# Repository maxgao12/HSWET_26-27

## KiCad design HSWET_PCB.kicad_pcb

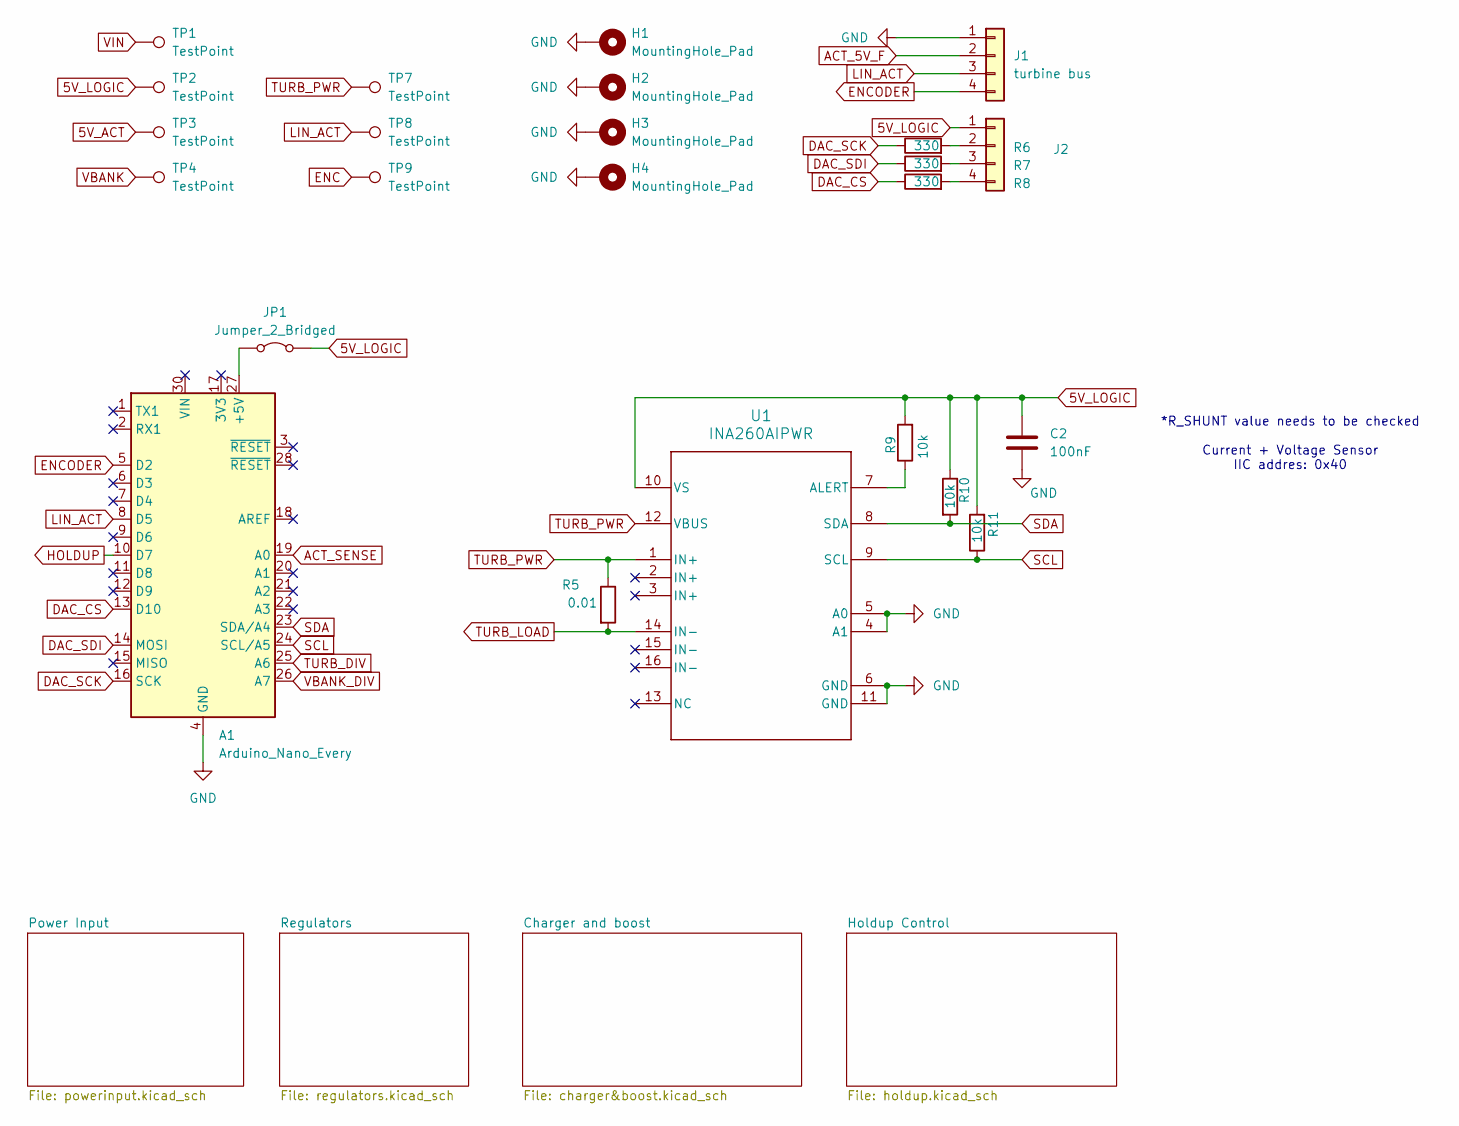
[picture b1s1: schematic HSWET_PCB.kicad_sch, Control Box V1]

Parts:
A1: Arduino_Nano_Every; Arduino_Nano
C2: 100nF; C_0603_1608Metric
H1, H2, H3, H4: MountingHole_Pad; MountingHole_2.5mm_Pad
J1: turbine bus; PinHeader_1x04_P2.54mm_Vertical
J2: turbine bus; PinSocket_1x04_P2.54mm_Vertical
JP1: Jumper_2_Bridged; PinHeader_1x02_P2.54mm_Vertical
R5: 0.01; R_0603_1608Metric
R6, R7, R8: 330; R_0603_1608Metric
R9, R10, R11: 10k; R_0603_1608Metric
TP1, TP2, TP3, TP4, TP7, TP8, TP9: TestPoint; TestPoint_Pad_1.0x1.0mm
U1: INA260AIPWR; ina260

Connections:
5V_ACT: TP3.1 (1_1); also elsewhere on the board
5V_LOGIC: C2.2, J2.1, JP1.2 (B), R9.2, R10.1, R11.2, TP2.1 (1_1), U1.10 (VS); also elsewhere on the board
ACT_5V_F: J1.2; also elsewhere on the board
ACT_SENSE: A1.19 (A0); also elsewhere on the board
DAC_CS: A1.13 (D10), R8.1
DAC_SCK: A1.16 (SCK), R6.1
DAC_SDI: A1.14 (MOSI), R7.1
ENC: TP9.1 (1_1)
ENCODER: A1.5 (D2), J1.4
GND: A1.4 (GND), A1.29 (GND), C2.1, H1.1 (1_1), H2.1 (1_1), H3.1 (1_1), H4.1 (1_1), J1.1, U1.4 (A1), U1.5 (A0), U1.6 (GND), U1.11 (GND); also elsewhere on the board
HOLDUP: A1.10 (D7); also elsewhere on the board
LIN_ACT: A1.8 (D5), J1.3, TP8.1 (1_1)
unnamed: A1.27 (+5V), JP1.1 (A)
unnamed: J2.2, R6.2
unnamed: J2.3, R7.2
unnamed: J2.4, R8.2
unnamed: R9.1, U1.7 (ALERT)
SCL: A1.24 (SCL/A5), R11.1, U1.9 (SCL)
SDA: A1.23 (SDA/A4), R10.2, U1.8 (SDA)
TURB_DIV: A1.25 (A6); also elsewhere on the board
TURB_LOAD: R5.2, U1.14 (IN-); also elsewhere on the board
TURB_PWR: R5.1, TP7.1 (1_1), U1.1 (IN+), U1.12 (VBUS); also elsewhere on the board
VBANK: TP4.1 (1_1); also elsewhere on the board
VBANK_DIV: A1.26 (A7); also elsewhere on the board
VIN: TP1.1 (1_1); also elsewhere on the board

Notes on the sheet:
*R_SHUNT value needs to be checked Current + Voltage Sensor IIC addres: 0x40

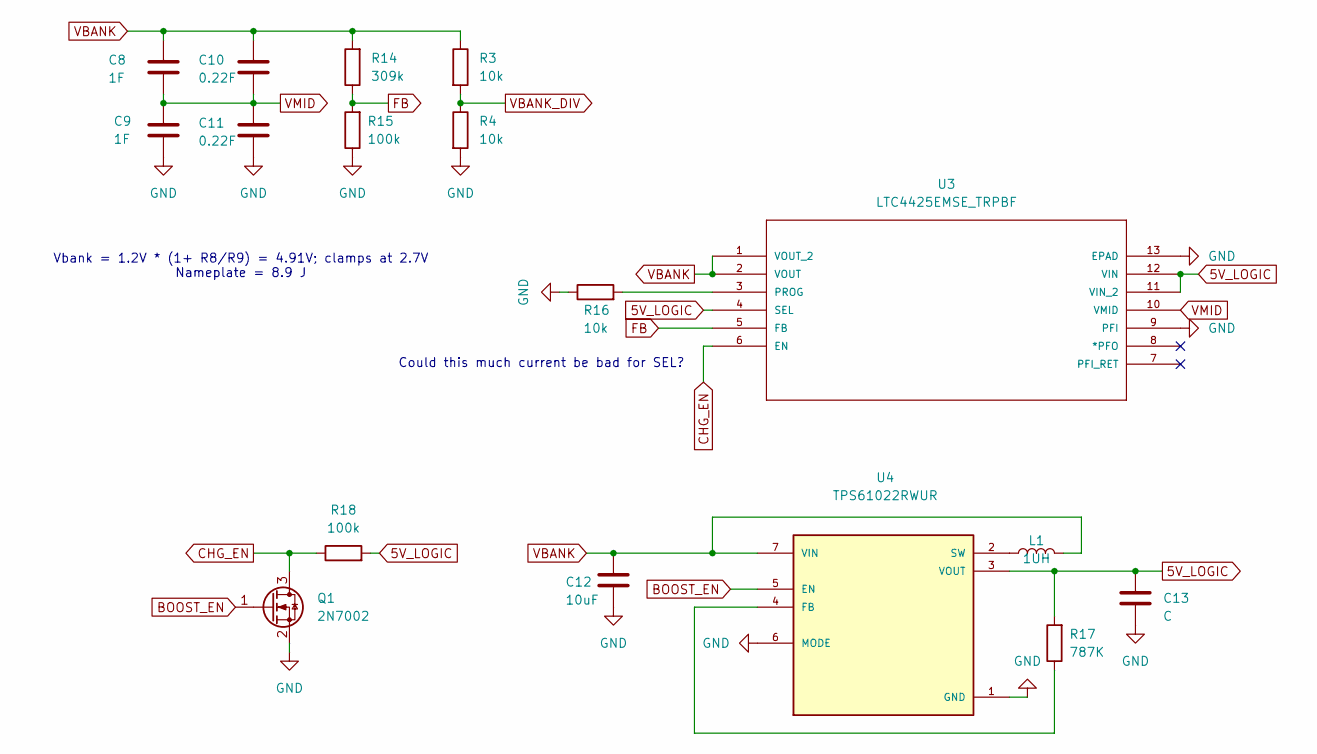
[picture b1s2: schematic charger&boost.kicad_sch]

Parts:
C8, C9: 1F; CAP_DGH-17X17X8.5_ILC
C10, C11: 0.22F; C_0603_1608Metric
C12: 10uF; C_0603_1608Metric
C13: C; C_0603_1608Metric
L1: 1UH; L_Changjiang_FTC201610D
Q1: 2N7002; SOT-23
R3, R4, R16: 10k; R_0603_1608Metric
R14: 309k; R_0603_1608Metric
R15, R18: 100k; R_0603_1608Metric
R17: 787K; R_0603_1608Metric
U3: LTC4425EMSE_TRPBF; MSOP-12_MSE; MANUFACTURER_PART_NUMBER ltc4425emse#pbf
U4: TPS61022RWUR; CONV_TPS61022RWUR; PARTREV 4223724/C 02/2018

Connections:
5V_LOGIC: C13.1, R17.2, R18.2, U3.4 (SEL), U3.11 (VIN_2), U3.12 (VIN), U4.3 (VOUT); also elsewhere on the board
BOOST_EN: Q1.1 (G), U4.5 (EN); also elsewhere on the board
CHG_EN: Q1.3 (D), R18.1, U3.6 (EN)
FB: R14.1, R15.2, U3.5 (FB)
GND: C9.2, C11.2, C12.2, C13.2, Q1.2 (S), R4.2, R15.1, R16.1, U3.9 (PFI), U3.13 (EPAD), U4.1 (GND), U4.6 (MODE); also elsewhere on the board
unnamed: R16.2, U3.3 (PROG)
unnamed: R17.1, U4.4 (FB)
unnamed: L1.2, U4.2 (SW)
VBANK: C8.1, C10.1, C12.1, L1.1, R3.1, R14.2, U3.1 (VOUT_2), U3.2 (VOUT), U4.7 (VIN); also elsewhere on the board
VBANK_DIV: R3.2, R4.1; also elsewhere on the board
VMID: C8.2, C9.1, C10.2, C11.1, U3.10 (VMID)

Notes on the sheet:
Vbank = 1.2V * (1+ R8/R9) = 4.91V; clamps at 2.7V Nameplate = 8.9 J
Could this much current be bad for SEL?

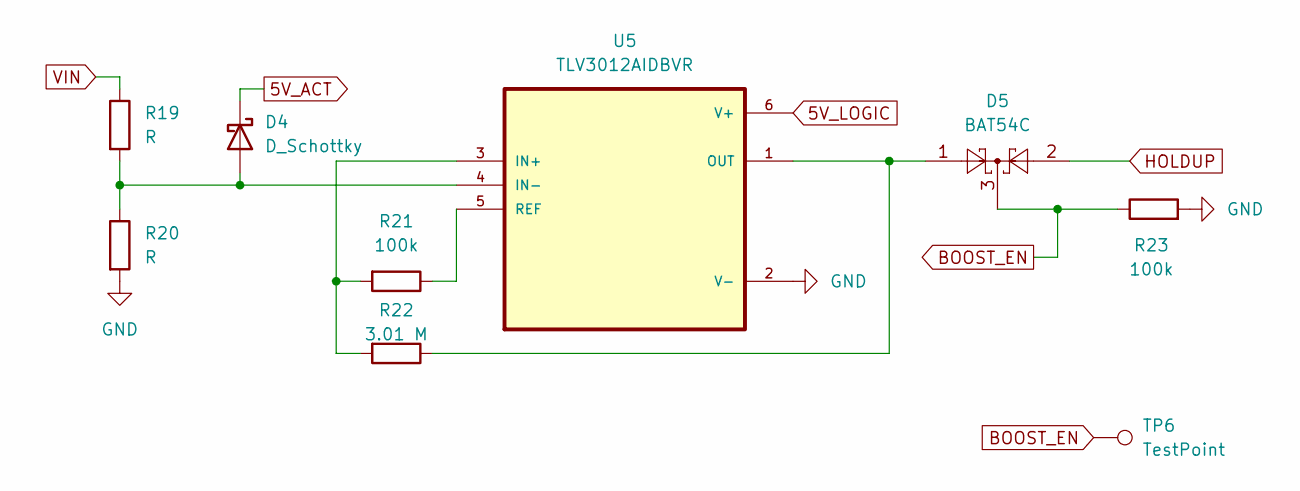
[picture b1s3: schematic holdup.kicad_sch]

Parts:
D4: D_Schottky; DIOM5436X330N
D5: BAT54C; SOT-23
R19, R20: R; R_0603_1608Metric
R21, R23: 100k; R_0603_1608Metric
R22: 3.01 M; R_0603_1608Metric
TP6: TestPoint; TestPoint_Pad_1.0x1.0mm
U5: TLV3012AIDBVR; SOT95P280X145-6N

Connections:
5V_ACT: D4.1 (K); also elsewhere on the board
5V_LOGIC: U5.6 (V+); also elsewhere on the board
BOOST_EN: D5.3, R23.1, TP6.1 (1_1); also elsewhere on the board
GND: R20.2, R23.2, U5.2 (V-); also elsewhere on the board
HOLDUP: D5.2; also elsewhere on the board
unnamed: D4.2 (A), R19.2, R20.1, U5.4 (IN-)
unnamed: R21.2, R22.2, U5.3 (IN+)
unnamed: D5.1, R22.1, U5.1 (OUT)
unnamed: R21.1, U5.5 (REF)
VIN: R19.1; also elsewhere on the board

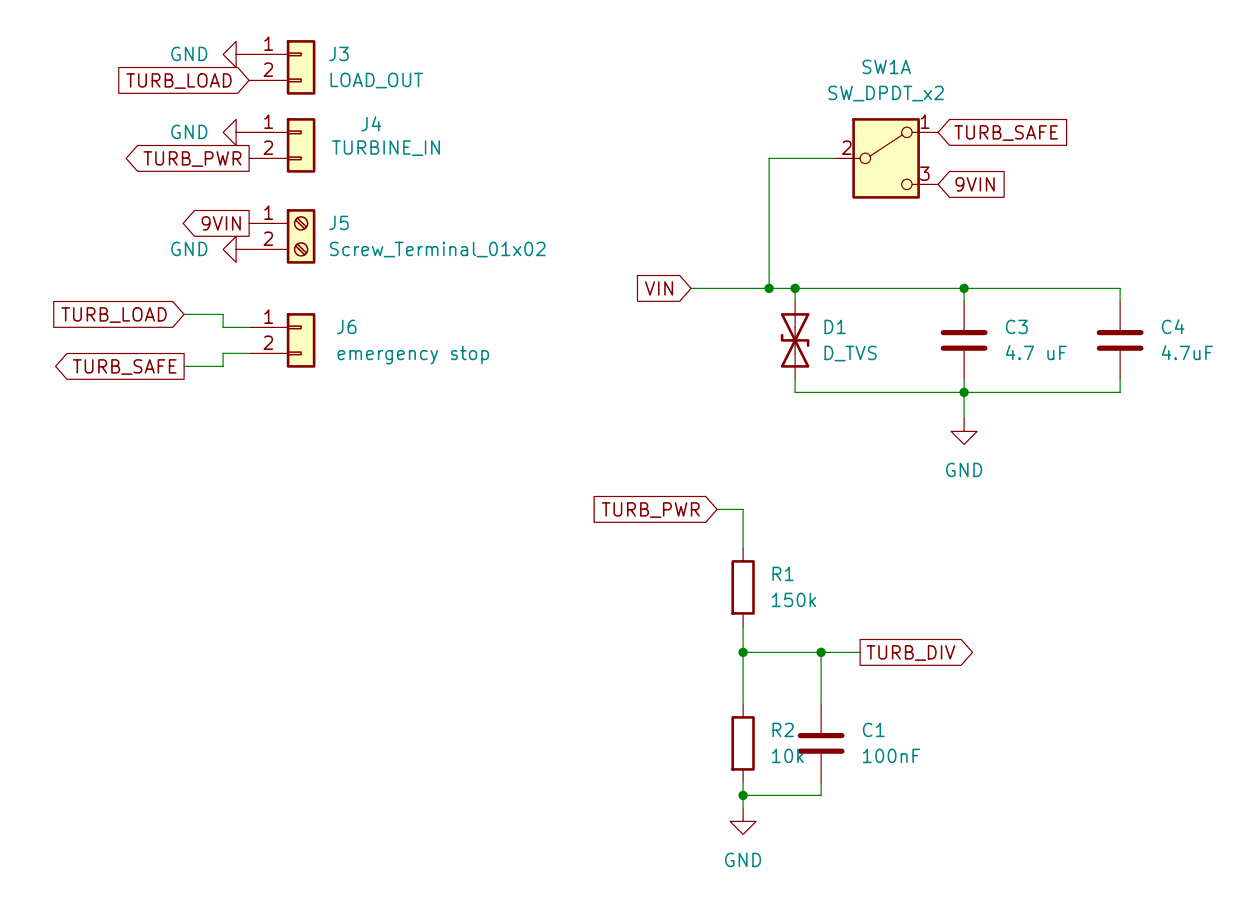
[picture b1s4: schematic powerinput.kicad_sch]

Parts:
C1: 100nF; C_0603_1608Metric
C3: 4.7 uF; C_0603_1608Metric
C4: 4.7uF; C_0603_1608Metric
D1: D_TVS; D_SMB_Handsoldering
J3: LOAD_OUT; AMASS_XT30PW-M_1x02_P2.50mm_Horizontal
J4: TURBINE_IN; AMASS_XT30PW-F_1x02_P2.50mm_Horizontal
J5: Screw_Terminal_01x02; 1760510000
J6: emergency stop; JST_EH_B2B-EH-A_1x02_P2.50mm_Vertical
R1: 150k; R_0603_1608Metric
R2: 10k; R_0603_1608Metric
SW1: SW_DPDT_x2; 1101A2CQEA

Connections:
9VIN: J5.1, SW1.3 (C)
GND: C1.2, C3.2, C4.2, D1.2 (A2), J3.1, J4.1, J5.2, R2.2; also elsewhere on the board
TURB_DIV: C1.1, R1.2, R2.1; also elsewhere on the board
TURB_LOAD: J3.2, J6.1; also elsewhere on the board
TURB_PWR: J4.2, R1.1; also elsewhere on the board
TURB_SAFE: J6.2, SW1.1 (A)
VIN: C3.1, C4.1, D1.1 (A1), SW1.2 (B); also elsewhere on the board

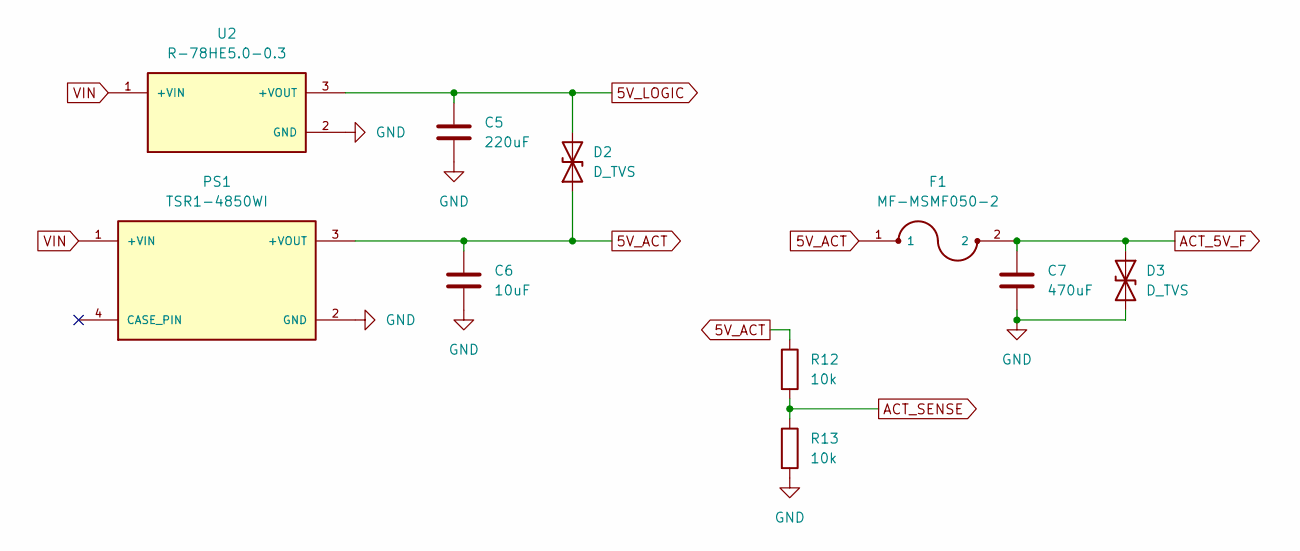
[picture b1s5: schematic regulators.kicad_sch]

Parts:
C5: 220uF; C_0603_1608Metric
C6: 10uF; C_0603_1608Metric
C7: 470uF; C_0603_1608Metric
D2, D3: D_TVS; D_0201_0603Metric_Pad0.64x0.40mm_HandSolder
F1: MF-MSMF050-2; FUSM4632X85
PS1: TSR1-4850WI; CONV_TSR1-4850WI; PARTREV April 7, 2021
R12, R13: 10k; R_0603_1608Metric
U2: R-78HE5.0-0.3; SIP900W75P254L1200H1300Q3; PARTREV 0/2019

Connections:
5V_ACT: C6.1, D2.1 (A1), F1.1, PS1.3 (+VOUT), R12.1; also elsewhere on the board
5V_LOGIC: C5.1, D2.2 (A2), U2.3 (+VOUT); also elsewhere on the board
ACT_5V_F: C7.1, D3.1 (A1), F1.2; also elsewhere on the board
ACT_SENSE: R12.2, R13.1; also elsewhere on the board
GND: C5.2, C6.2, C7.2, D3.2 (A2), PS1.2 (GND), R13.2, U2.2 (GND); also elsewhere on the board
VIN: PS1.1 (+VIN), U2.1 (+VIN); also elsewhere on the board

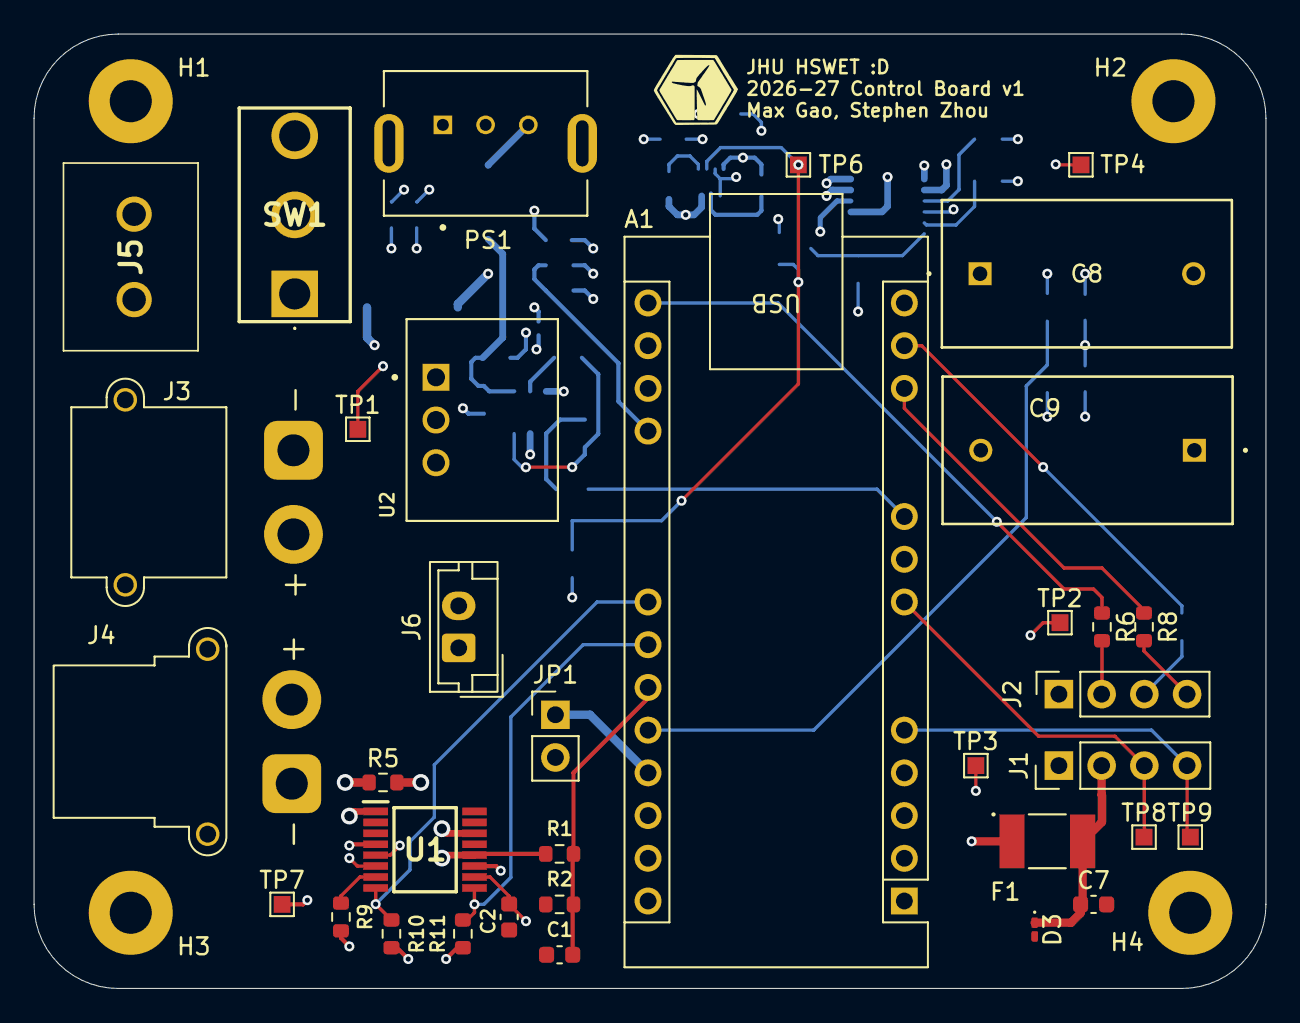
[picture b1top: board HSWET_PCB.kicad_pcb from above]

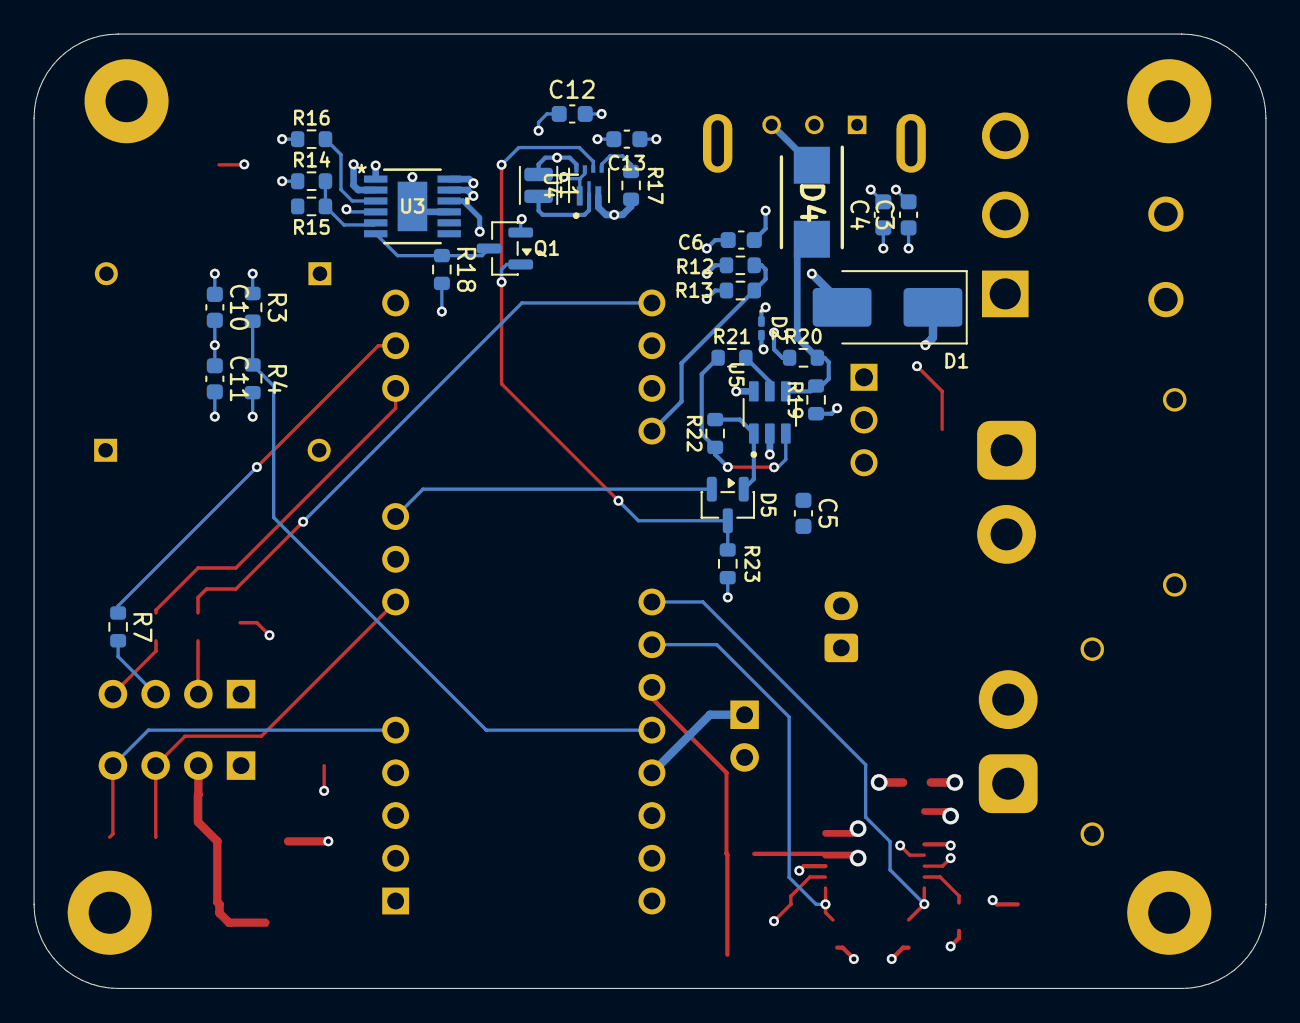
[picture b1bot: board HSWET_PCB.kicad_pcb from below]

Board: 4 copper layers, 73.2 x 56.8 mm, 71 parts (32 on the bottom side), 37 nets.

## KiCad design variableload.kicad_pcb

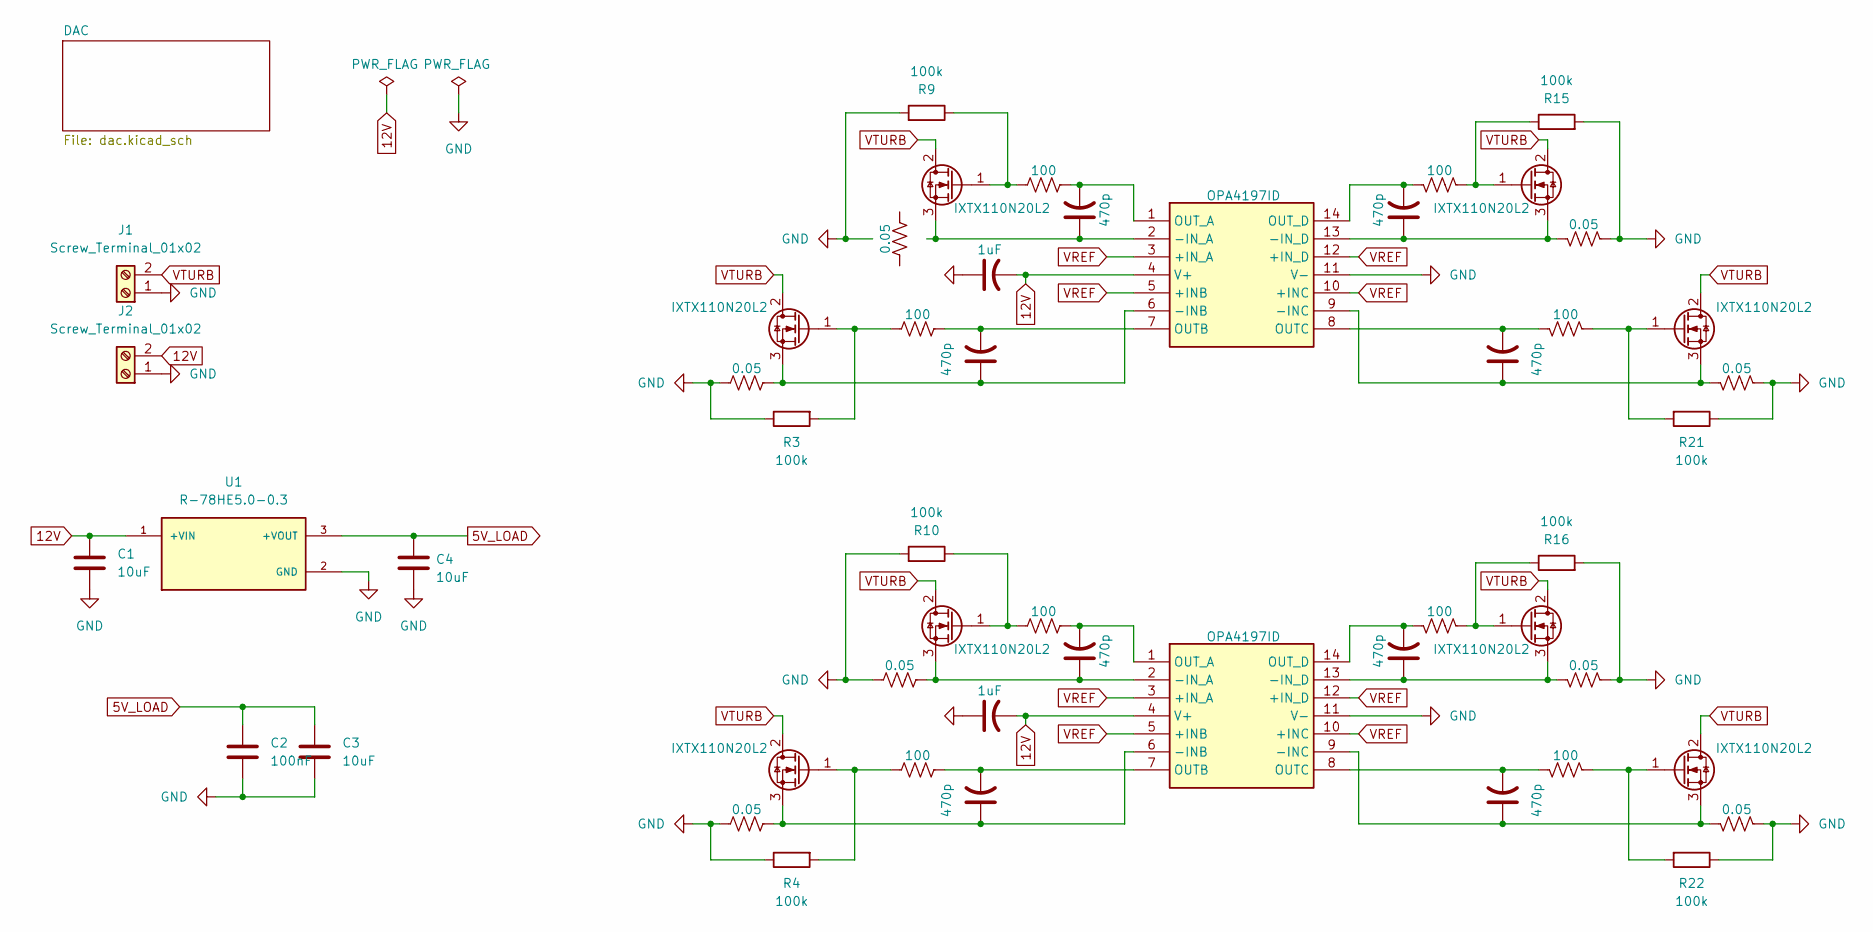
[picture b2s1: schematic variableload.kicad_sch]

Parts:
C1, C3, C4: 10uF; C_0805_2012Metric
C2: 100nF; C_0805_2012Metric
C5, C6, C9, C10, C11, C12, C13, C14: 470p; C_0805_2012Metric
C7, C8: 1uF; C_0805_2012Metric
IC1, IC2: OPA4197ID; SOIC-14_3.9x8.7mm_P1.27mm; Manufacturer_Part_Number OPA4172IDR; Mouser Part Number 595-OPA4172IDR
J1, J2: Screw_Terminal_01x02; TerminalBlock_Phoenix_MKDS-3-2-5.08_1x02_P5.08mm_Horizontal
Q1, Q2, Q3, Q4, Q5, Q6, Q7, Q8: IXTX110N20L2; TO-247-3_Vertical
R1, R2, R5, R6, R19, R20, R23, R24: 0.05; R_2512_6332Metric
R3, R4, R9, R10, R15, R16, R21, R22: 100k; R_0805_2012Metric
R7, R8, R11, R12, R13, R14, R17, R18: 100; R_0805_2012Metric
U1: R-78HE5.0-0.3; SIP900W75P254L1200H1300Q3; PARTREV 0/2019

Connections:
5V_LOAD: C2.1, C3.1, C4.1, U1.3 (+VOUT); also elsewhere on the board
12V: C1.1, C7.2, C8.2, IC1.4 (V+), IC2.4 (V+), J2.2, U1.1 (+VIN); also elsewhere on the board
GND: C1.2, C2.2, C3.2, C4.2, C7.1, C8.1, IC1.11 (V-), IC2.11 (V-), J1.1, J2.1, R1.2, R2.2, R3.1, R4.1, R5.2, R6.2, R9.2, R10.2, R15.2, R16.2, R19.2, R20.2, R21.1, R22.1, R23.2, R24.2, U1.2 (GND); also elsewhere on the board
unnamed: C5.1, IC1.6 (-INB), Q1.3 (S), R1.1
unnamed: C13.1, IC1.9 (-INC), Q7.3 (S), R23.1
unnamed: C11.1, IC1.13 (-IN_D), Q5.3 (S), R19.1
unnamed: C5.2, IC1.7 (OUTB), R7.1
unnamed: C13.2, IC1.8 (OUTC), R17.1
unnamed: C9.2, IC1.1 (OUT_A), R11.1
unnamed: C11.2, IC1.14 (OUT_D), R13.1
unnamed: C6.1, IC2.6 (-INB), Q2.3 (S), R2.1
unnamed: C14.1, IC2.9 (-INC), Q8.3 (S), R24.1
unnamed: C10.1, IC2.2 (-IN_A), Q4.3 (S), R6.1
unnamed: C12.1, IC2.13 (-IN_D), Q6.3 (S), R20.1
unnamed: C6.2, IC2.7 (OUTB), R8.1
unnamed: C14.2, IC2.8 (OUTC), R18.1
unnamed: C10.2, IC2.1 (OUT_A), R12.1
unnamed: C12.2, IC2.14 (OUT_D), R14.1
unnamed: Q1.1 (G), R3.2, R7.2
unnamed: Q2.1 (G), R4.2, R8.2
unnamed: Q3.1 (G), R9.1, R11.2
unnamed: Q4.1 (G), R10.1, R12.2
unnamed: Q5.1 (G), R13.2, R15.1
unnamed: Q6.1 (G), R14.2, R16.1
unnamed: Q7.1 (G), R17.2, R21.2
unnamed: Q8.1 (G), R18.2, R22.2
VREF: IC1.3 (+IN_A), IC1.5 (+INB), IC1.10 (+INC), IC1.12 (+IN_D), IC2.3 (+IN_A), IC2.5 (+INB), IC2.10 (+INC), IC2.12 (+IN_D); also elsewhere on the board
VTURB: J1.2, Q1.2 (D), Q2.2 (D), Q3.2 (D), Q4.2 (D), Q5.2 (D), Q6.2 (D), Q7.2 (D), Q8.2 (D); also elsewhere on the board

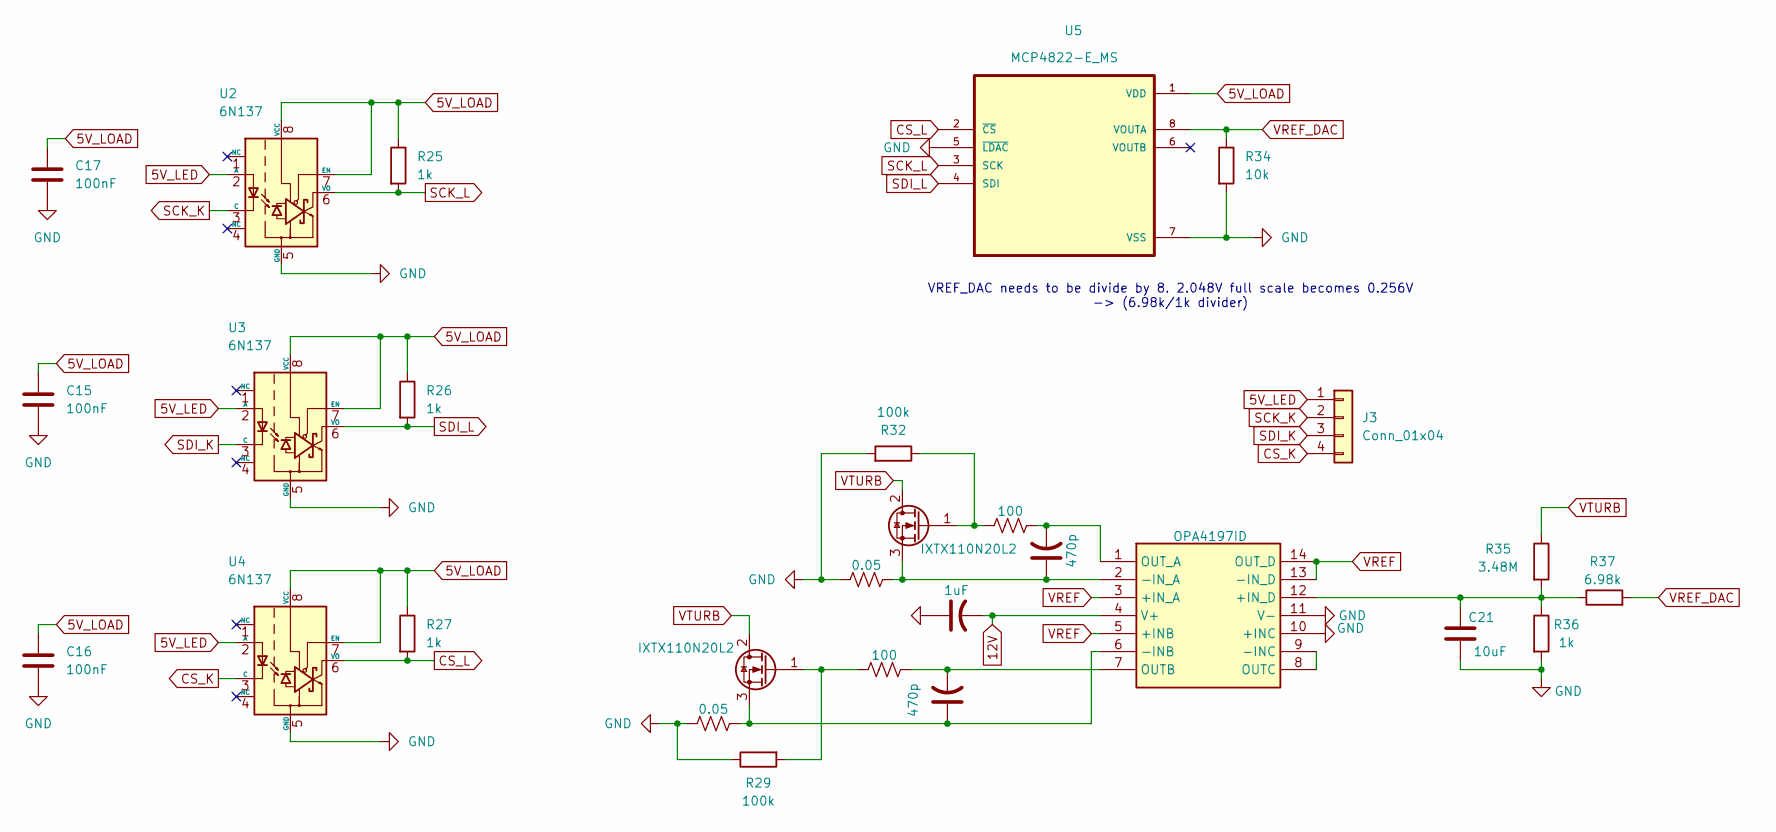
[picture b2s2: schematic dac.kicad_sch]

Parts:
C15, C16, C17: 100nF; C_0805_2012Metric
C18, C20: 470p; C_0805_2012Metric
C19: 1uF; C_0805_2012Metric
C21: 10uF; C_0805_2012Metric
IC3: OPA4197ID; SOIC-14_3.9x8.7mm_P1.27mm; Manufacturer_Part_Number OPA4172IDR; Mouser Part Number 595-OPA4172IDR
J3: Conn_01x04; JST_XH_B4B-XH-A_1x04_P2.50mm_Vertical
Q9, Q10: IXTX110N20L2; TO-247-3_Vertical
R25, R26, R27, R36: 1k; R_0805_2012Metric
R28, R30: 0.05; R_2512_6332Metric
R29, R32: 100k; R_0805_2012Metric
R31, R33: 100; R_0805_2012Metric
R34: 10k; R_0805_2012Metric
R35: 3.48M; R_1206_3216Metric
R37: 6.98k; R_0805_2012Metric
U2, U3, U4: 6N137; DIP-8_W7.62mm
U5: MCP4822-E_MS; SOP65P490X110-8N

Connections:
5V_LED: J3.1, U2.2 (A), U3.2 (A), U4.2 (A)
5V_LOAD: C15.1, C16.1, C17.1, R25.1, R26.1, R27.1, U2.7 (EN), U2.8 (VCC), U3.7 (EN), U3.8 (VCC), U4.7 (EN), U4.8 (VCC), U5.1 (VDD); also elsewhere on the board
12V: C19.2, IC3.4 (V+); also elsewhere on the board
CS_K: J3.4, U4.3 (C)
CS_L: R27.2, U4.6 (VO), U5.2 (~CS)
GND: C15.2, C16.2, C17.2, C19.1, C21.2, IC3.10 (+INC), IC3.11 (V-), R28.2, R29.1, R30.2, R32.2, R34.2, R36.2, U2.5 (GND), U3.5 (GND), U4.5 (GND), U5.5 (~LDAC), U5.7 (VSS); also elsewhere on the board
unnamed: C21.1, IC3.12 (+IN_D), R35.2, R36.1, R37.1
unnamed: C18.1, IC3.6 (-INB), Q9.3 (S), R28.1
unnamed: IC3.8 (OUTC), IC3.9 (-INC)
unnamed: C20.1, IC3.2 (-IN_A), Q10.3 (S), R30.1
unnamed: C18.2, IC3.7 (OUTB), R31.1
unnamed: C20.2, IC3.1 (OUT_A), R33.1
unnamed: Q9.1 (G), R29.2, R31.2
unnamed: Q10.1 (G), R32.1, R33.2
SCK_K: J3.2, U2.3 (C)
SCK_L: R25.2, U2.6 (VO), U5.3 (SCK)
SDI_K: J3.3, U3.3 (C)
SDI_L: R26.2, U3.6 (VO), U5.4 (SDI)
VREF: IC3.3 (+IN_A), IC3.5 (+INB), IC3.13 (-IN_D), IC3.14 (OUT_D); also elsewhere on the board
VREF_DAC: R34.1, R37.2, U5.8 (VOUTA)
VTURB: Q9.2 (D), Q10.2 (D), R35.1; also elsewhere on the board

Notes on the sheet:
VREF_DAC needs to be divide by 8. 2.048V full scale becomes 0.256V -> (6.98k/1k divider)

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
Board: 4 copper layers, 76 parts (0 on the bottom side), 41 nets, no tracks yet.
